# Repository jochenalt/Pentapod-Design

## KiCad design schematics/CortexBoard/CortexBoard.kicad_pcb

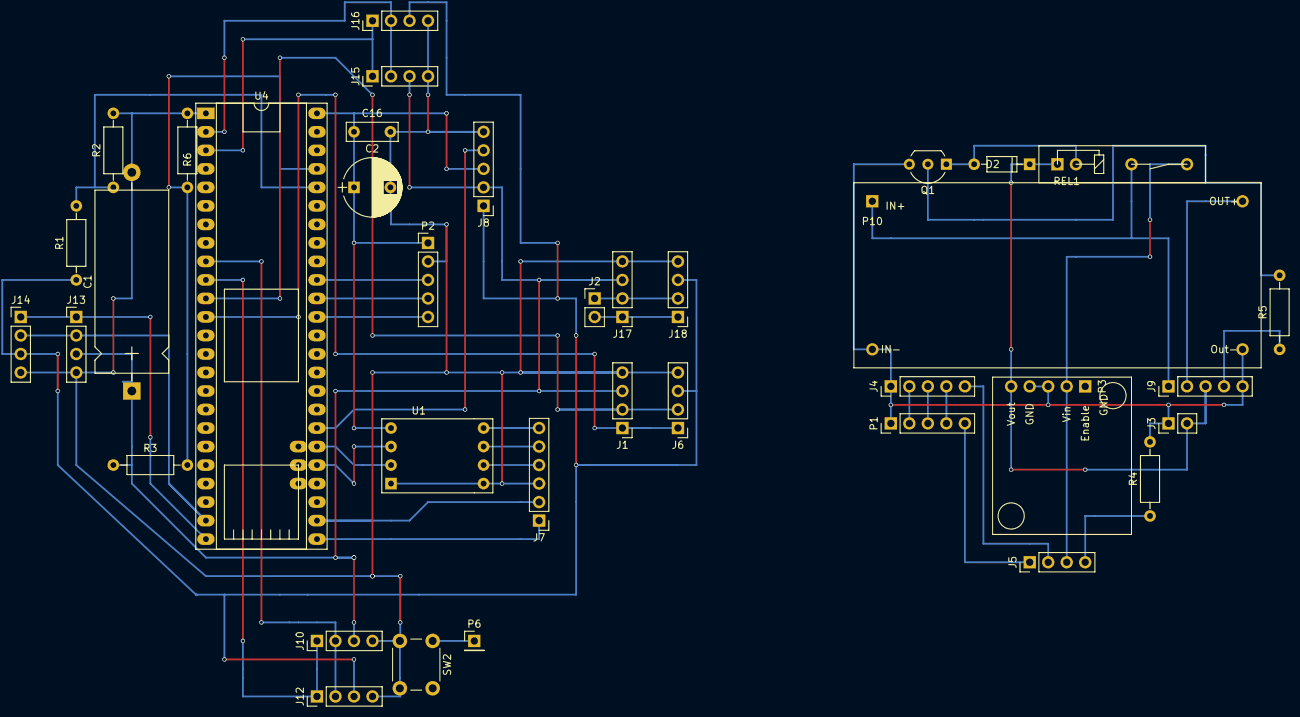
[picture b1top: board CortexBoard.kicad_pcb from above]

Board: 2 copper layers, 37 parts (0 on the bottom side), 42 nets.

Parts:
C1: 2200uF; CP_Axial_L25.0mm_D10.0mm_P30.00mm_Horizontal
C2: 220uF; CP_Radial_D8.0mm_P5.00mm
C16: 100nF; C_Rect_L7.0mm_W2.5mm_P5.00mm
D2: D_Schottky; D_DO-35_SOD27_P7.62mm_Horizontal
J1: LEG1-LO; Pin_Header_Straight_1x04_Pitch2.54mm
J2: UART6 Connector; Pin_Header_Straight_1x02_Pitch2.54mm
J3: Odroid Power; Pin_Header_Straight_1x02_Pitch2.54mm
J4: Bodysocket; Pin_Header_Straight_1x05_Pitch2.54mm
J5: LED/Switch; Pin_Header_Straight_1x04_Pitch2.54mm
J6: LEG1-HI; Pin_Header_Straight_1x04_Pitch2.54mm
J7: CORTEX CLI; Pin_Header_Straight_1x06_Pitch2.54mm
J8: Cortex-Power-In; Pin_Header_Straight_1x05_Pitch2.54mm
J9: Cortex-Power-Out; Pin_Header_Straight_1x05_Pitch2.54mm
J10: LEG2-LO; Pin_Header_Straight_1x04_Pitch2.54mm
J12: LEG2-HI; Pin_Header_Straight_1x04_Pitch2.54mm
J13: LEG3-LO; Pin_Header_Straight_1x04_Pitch2.54mm
J14: LEG3-HI; Pin_Header_Straight_1x04_Pitch2.54mm
J15: LEG4-LO; Pin_Header_Straight_1x04_Pitch2.54mm
J16: LEG4-HI; Pin_Header_Straight_1x04_Pitch2.54mm
J17: LEG5-LO; Pin_Header_Straight_1x04_Pitch2.54mm
J18: LEG5-HI; Pin_Header_Straight_1x04_Pitch2.54mm
P1: Battery; Pin_Header_Straight_1x05_Pitch2.54mm
P2: BNO055; Pin_Header_Straight_1x05_Pitch2.54mm
P3: D24V50F5; Pololu_D24V50F5
P6: Teensy RST(49); Pin_Header_Straight_1x01_Pitch2.54mm
P10: XL4015
Q1: BC337(o.ä.); TO-92_Inline_Wide
R1, R3: 150K; R_Axial_DIN0207_L6.3mm_D2.5mm_P10.16mm_Horizontal
R2, R6: 10K; R_Axial_DIN0207_L6.3mm_D2.5mm_P10.16mm_Horizontal
R4: 3.3K; R_Axial_DIN0207_L6.3mm_D2.5mm_P10.16mm_Horizontal
R5: 1K; R_Axial_DIN0207_L6.3mm_D2.5mm_P10.16mm_Horizontal
REL1: HF49FD; Relay_HF49FD
SW2: reset; SW_PUSH_6mm
U1: I2C_LevelShifter
U4: Teensy_3.5

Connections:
/3.3V_ODroid: J7.6, U1.8
/+5V: D2.1, J3.2, J9.3, P3.5, REL1.1
/+10V: C1.1, J1.3, J8.2, J10.3, J13.3, J15.3, J17.3, R3.1
/+14V: J6.3, J8.1, J12.3, J14.3, J16.3, J18.3, R1.1
/Batt1: J4.2, P1.2
/Batt2: J4.3, P1.3
/Batt3: J4.4, P1.4
/Batt+: J4.5, J5.2
/Batt-: J3.1, J4.1, J9.5, P1.1, P3.3, P3.4, P10.2, P10.3, Q1.3, R4.2
/GND: C1.2, C2.2, C16.2, J1.4, J6.4, J7.3, J8.5, J10.4, J12.4, J13.4, J14.4, J15.4, J16.4, J17.4, J18.4, P2.2, R2.2, R6.2, SW2.2, U1.1, U1.5, U4.1, U4.34
/LEDKathode: J5.4, R4.1
/RST: P2.5, U4.37
/RX1: J15.1, J16.1, U4.3
/RX2: J1.1, J6.1, U4.12
/RX3: J10.1, J12.1, U4.10
/RX4: J13.1, J14.1, U4.24
/RX5: J7.2, U4.26
/RX6: J2.2, J17.1, J18.1, U4.51
/Relay-Out: J8.4, U4.31
/SCL: P2.4, U4.38
/SCL0: U1.3, U4.29
/SCL-ODroid: J7.5, U1.7
/SDA: P2.3, U4.39
/SDA0: U1.2, U4.30
/SDA-ODroid: J7.4, U1.6
/SW1/VIN/LEDAnode: J5.3, P3.2, REL1.4
/SW2/Batt: J5.1, P1.5
/TX1: J15.2, J16.2, U4.2
/TX2: J1.2, J6.2, U4.11
/TX3: J10.2, J12.2, U4.9
/TX4: J13.2, J14.2, U4.23
/TX5: J7.1, U4.25
/TX6: J2.1, J17.2, J18.2, U4.50
/VIn+5V: C2.1, C16.1, J8.3, P2.1, U1.4, U4.48
/Vout+10V: J9.2, P10.4
/Vout+14V: J9.1, P10.1, REL1.3
unnamed: D2.2, Q1.1, REL1.2
unnamed: J9.4, R5.1
unnamed: P6.1, SW2.1
unnamed: Q1.2, R5.2
unnamed: R1.2, R2.1, U4.44
unnamed: R3.2, R6.1, U4.45

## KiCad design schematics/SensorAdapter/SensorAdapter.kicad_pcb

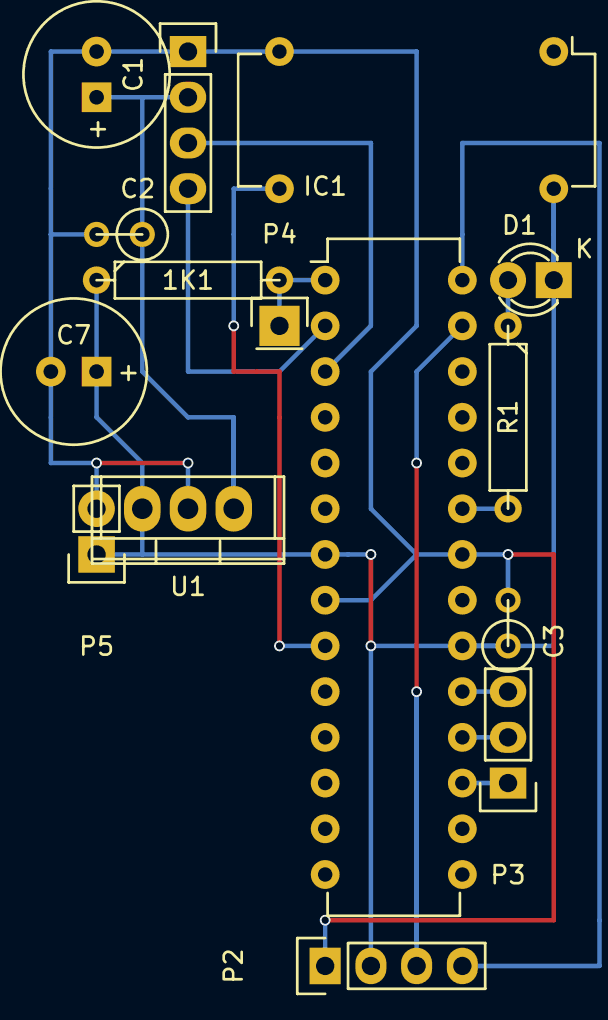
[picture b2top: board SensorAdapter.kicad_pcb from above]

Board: 2 copper layers, 15 parts (0 on the bottom side), 14 nets.

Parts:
1K1: 1K; R4
C1, C7: 47uF; C1V8
C2, C3: 100nF; R1
D1: LED; LED-3MM
IC1: ATMEGA328-P; DIP-28_W7.62mm
P1: ServoIN; Pin_Header_Straight_1x04
P2: VL6180X; Pin_Header_Straight_1x04
P3: ISP; Pin_Header_Straight_1x03
P4: RST; Pin_Header_Straight_1x01
P5: VDD-GND; Pin_Header_Straight_1x02
R1: 1K; R4
U1: 7805; TO-220
X1: CRYSTAL_OSSCI; DIP-14_W7.62mm

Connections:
/+5V: 1K1.1, C3.1, C7.1, D1.1, IC1.7, IC1.20, P2.2, P5.1, U1.VO, X1.14
/MISO: IC1.18, P3.2
/MOSI: IC1.17, P3.1
/RX: IC1.2, P1.4
/SCK: IC1.19, P3.3
/SCL: IC1.28, P2.4
/SDA: IC1.27, P2.3
/TX: IC1.3, P1.3
/VDD: C1.1, C2.1, P1.2, U1.VI
GNDPWR: C1.2, C2.2, C3.2, C7.2, IC1.8, IC1.22, P1.1, P2.1, P5.2, U1.GND, X1.7
unnamed: 1K1.2, IC1.1, P4.1
unnamed: D1.2, R1.1
unnamed: IC1.9, X1.8
unnamed: IC1.23, R1.2

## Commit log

2017-08-30 initial
2017-08-30 schematics
2017-08-30 added cad
2017-08-31 layout improvements
2017-09-01 made new power supply board
2017-09-03 Body is too tight., gave it 5mm more headroom
2017-09-03 adapted body
2017-09-13 added documentation for navigation stack
2017-09-16 Made Body smaller again
2017-09-16 new Elko to stabilize servo voltage
2017-09-17 body changed such that it does not look like a vase anymore
2017-09-17 layout
2017-09-17 made body socket nicer
2017-09-19 changed socket board in body and made Hip to fit to the body's plane
2017-09-20 found CAD model of servo Herkulex DRS-0401 and integrated it
2017-09-22 Wire-hole for leg No.4 was too low
2017-09-24 a weekend's work
2017-09-25 Started preparation for DRS-0401 servo (already ordered)
2017-09-26 Big design change to support upcoming DRS-0401 servos
2017-09-27 made a nice view of all objects
2017-09-29 Many changes due to first test with DRS-0401
2017-09-30 first try with DRS-0401 PCB
2017-10-01 Weekend
2017-10-02 no message
2017-10-03 corrections after assembly of 040x leg
2017-10-03 updated kinematics docs
2017-10-03 beautified
2017-10-03 last minute changes before printing
2017-10-04 Tried a knee zylinder with fase
2017-10-05 new images
2017-10-06 new CAD pictures
2017-10-06 new videos
2017-10-07 doc on overview
2017-10-07 added STL files
2017-10-07 Removed red cross in some parts
2017-10-09 adapted Hip to get thicker walls
2017-10-10 small dimension corrections
2017-10-15 increased height of body by 4 mm to make more space for cortex
2017-10-18 lowered thread to make more space for cortex
2017-10-20 printed new body shape
2017-10-20 reshaped hip curve to match body-shape
2017-10-27 removed pre-040x parts
2017-10-28 removed legacy designs
2017-10-28 renamed, removed legacy
2017-10-29 added logical components
2017-11-05 corrected foot dampener, introduced design for Odroid XU4 and renamed old 040x stuff
2017-11-11 a litte more space for servo
2017-11-17 mode room for foot servo
2017-12-22 upated
2017-12-29 made all M3 screw holes 0,5mm bigger
2017-12-30 Amended some drill holes to use M6/8 screws only
